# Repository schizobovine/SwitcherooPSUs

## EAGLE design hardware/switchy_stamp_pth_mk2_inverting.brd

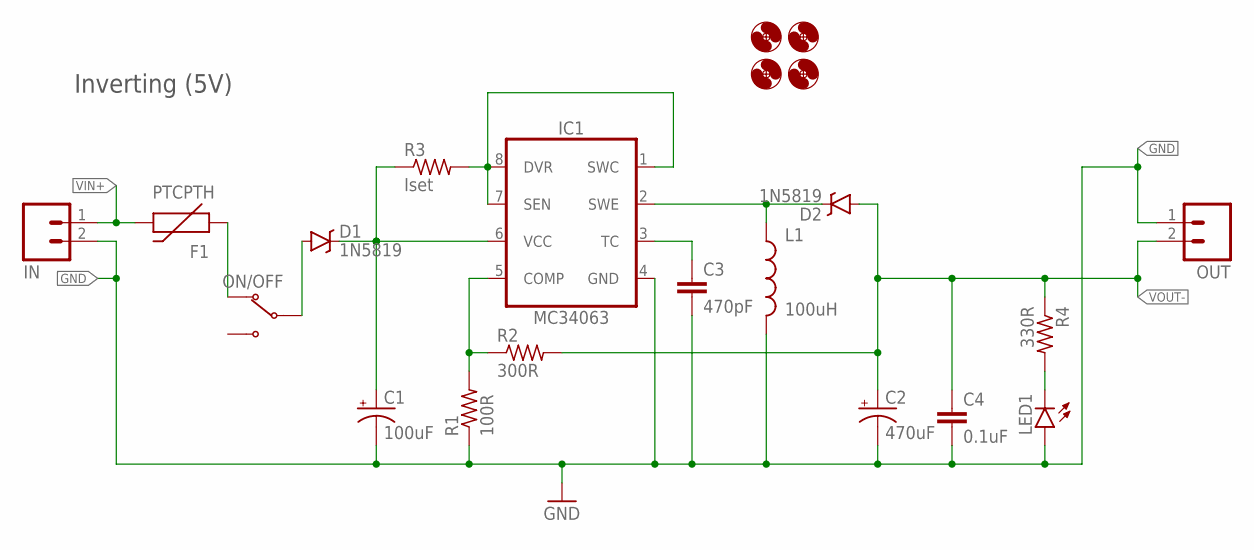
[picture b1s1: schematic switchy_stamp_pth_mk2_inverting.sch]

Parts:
C1: 100uF; E2,5-7
C2: 470uF; E2,5-7
C3: 470pF; C025-024X044
C4: 0.1uF; C025-024X044
D1, D2: 1N5819; DO-41
F1: PTCPTH; PTC
H1, H2, H3, H4: HOLE#2; HOLE-#2
IC1: MC34063; DIP-08
IN: M02JST-PTH-2; JST-2-PH-RA-PTH
L1: 100uH; RADIAL-PTH-3-BY-6.7DIA
LED1: LED3MM
ON/OFF: SWITCH-SPDTPTH-RA-2.54MM; SPDT-RA-2.54MM
OUT: M02JST-PTH-2; JST-2-PH-RA-PTH
R1: 100R; RESISTOR-AXIAL-PTH-7.68MM
R2: 300R; RESISTOR-AXIAL-PTH-7.68MM
R3: Iset; RESISTOR-AXIAL-PTH-7.68MM
R4: 330R; RESISTOR-AXIAL-PTH-7.68MM

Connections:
GND: C1.-, C2.-, C3.2, C4.2, IC1.4 (GND), IN.2, L1.P$2 (2), LED1.A, OUT.1, R1.P$1 (1)
unnamed: IC1.1 (SWC), IC1.7 (SEN), IC1.8 (DVR), R3.P$2 (2)
unnamed: C3.1, IC1.3 (TC)
unnamed: IC1.5 (COMP), R1.P$2 (2), R2.P$1 (1)
unnamed: F1.P$1 (1), ON/OFF.1 (NC)
unnamed: C1.+, D1.C, IC1.6 (VCC), R3.P$1 (1)
unnamed: D2.C, IC1.2 (SWE), L1.P$1 (1)
unnamed: LED1.K (C), R4.P$2 (2)
unnamed: D1.A, ON/OFF.2 (COM)
VIN+: F1.P$2 (2), IN.1
VOUT-: C2.+, C4.1, D2.A, OUT.2, R2.P$2 (2), R4.P$1 (1)

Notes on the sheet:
Inverting (5V)

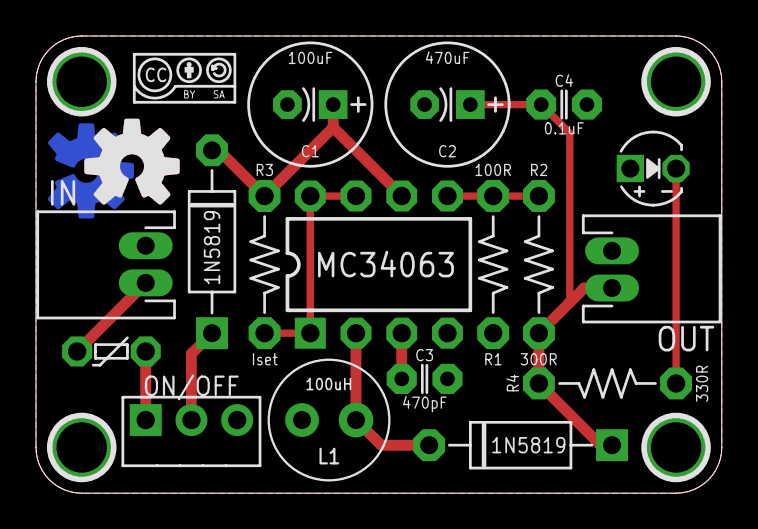
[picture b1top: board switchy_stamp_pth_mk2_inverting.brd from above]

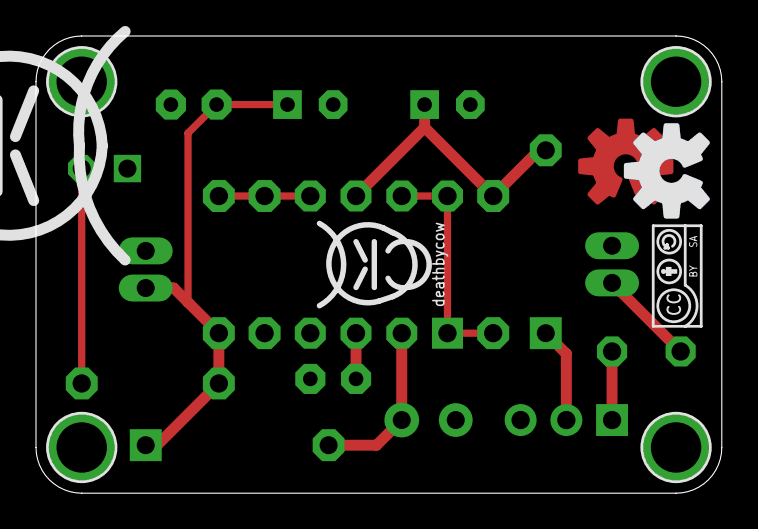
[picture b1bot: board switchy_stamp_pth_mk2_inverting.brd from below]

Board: 2 copper layers, 38.1 x 25.4 mm, 27 parts (3 on the bottom side), 11 nets.

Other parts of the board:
U$1, U$2: CC-BY-SA-4.0-NO-URL
U$3: COW
U$4: COW_SMALL
U$5: OSHWLOGO_BOT_0.2_A
U$6: OSHWLOGO_TOP_0.2_A
